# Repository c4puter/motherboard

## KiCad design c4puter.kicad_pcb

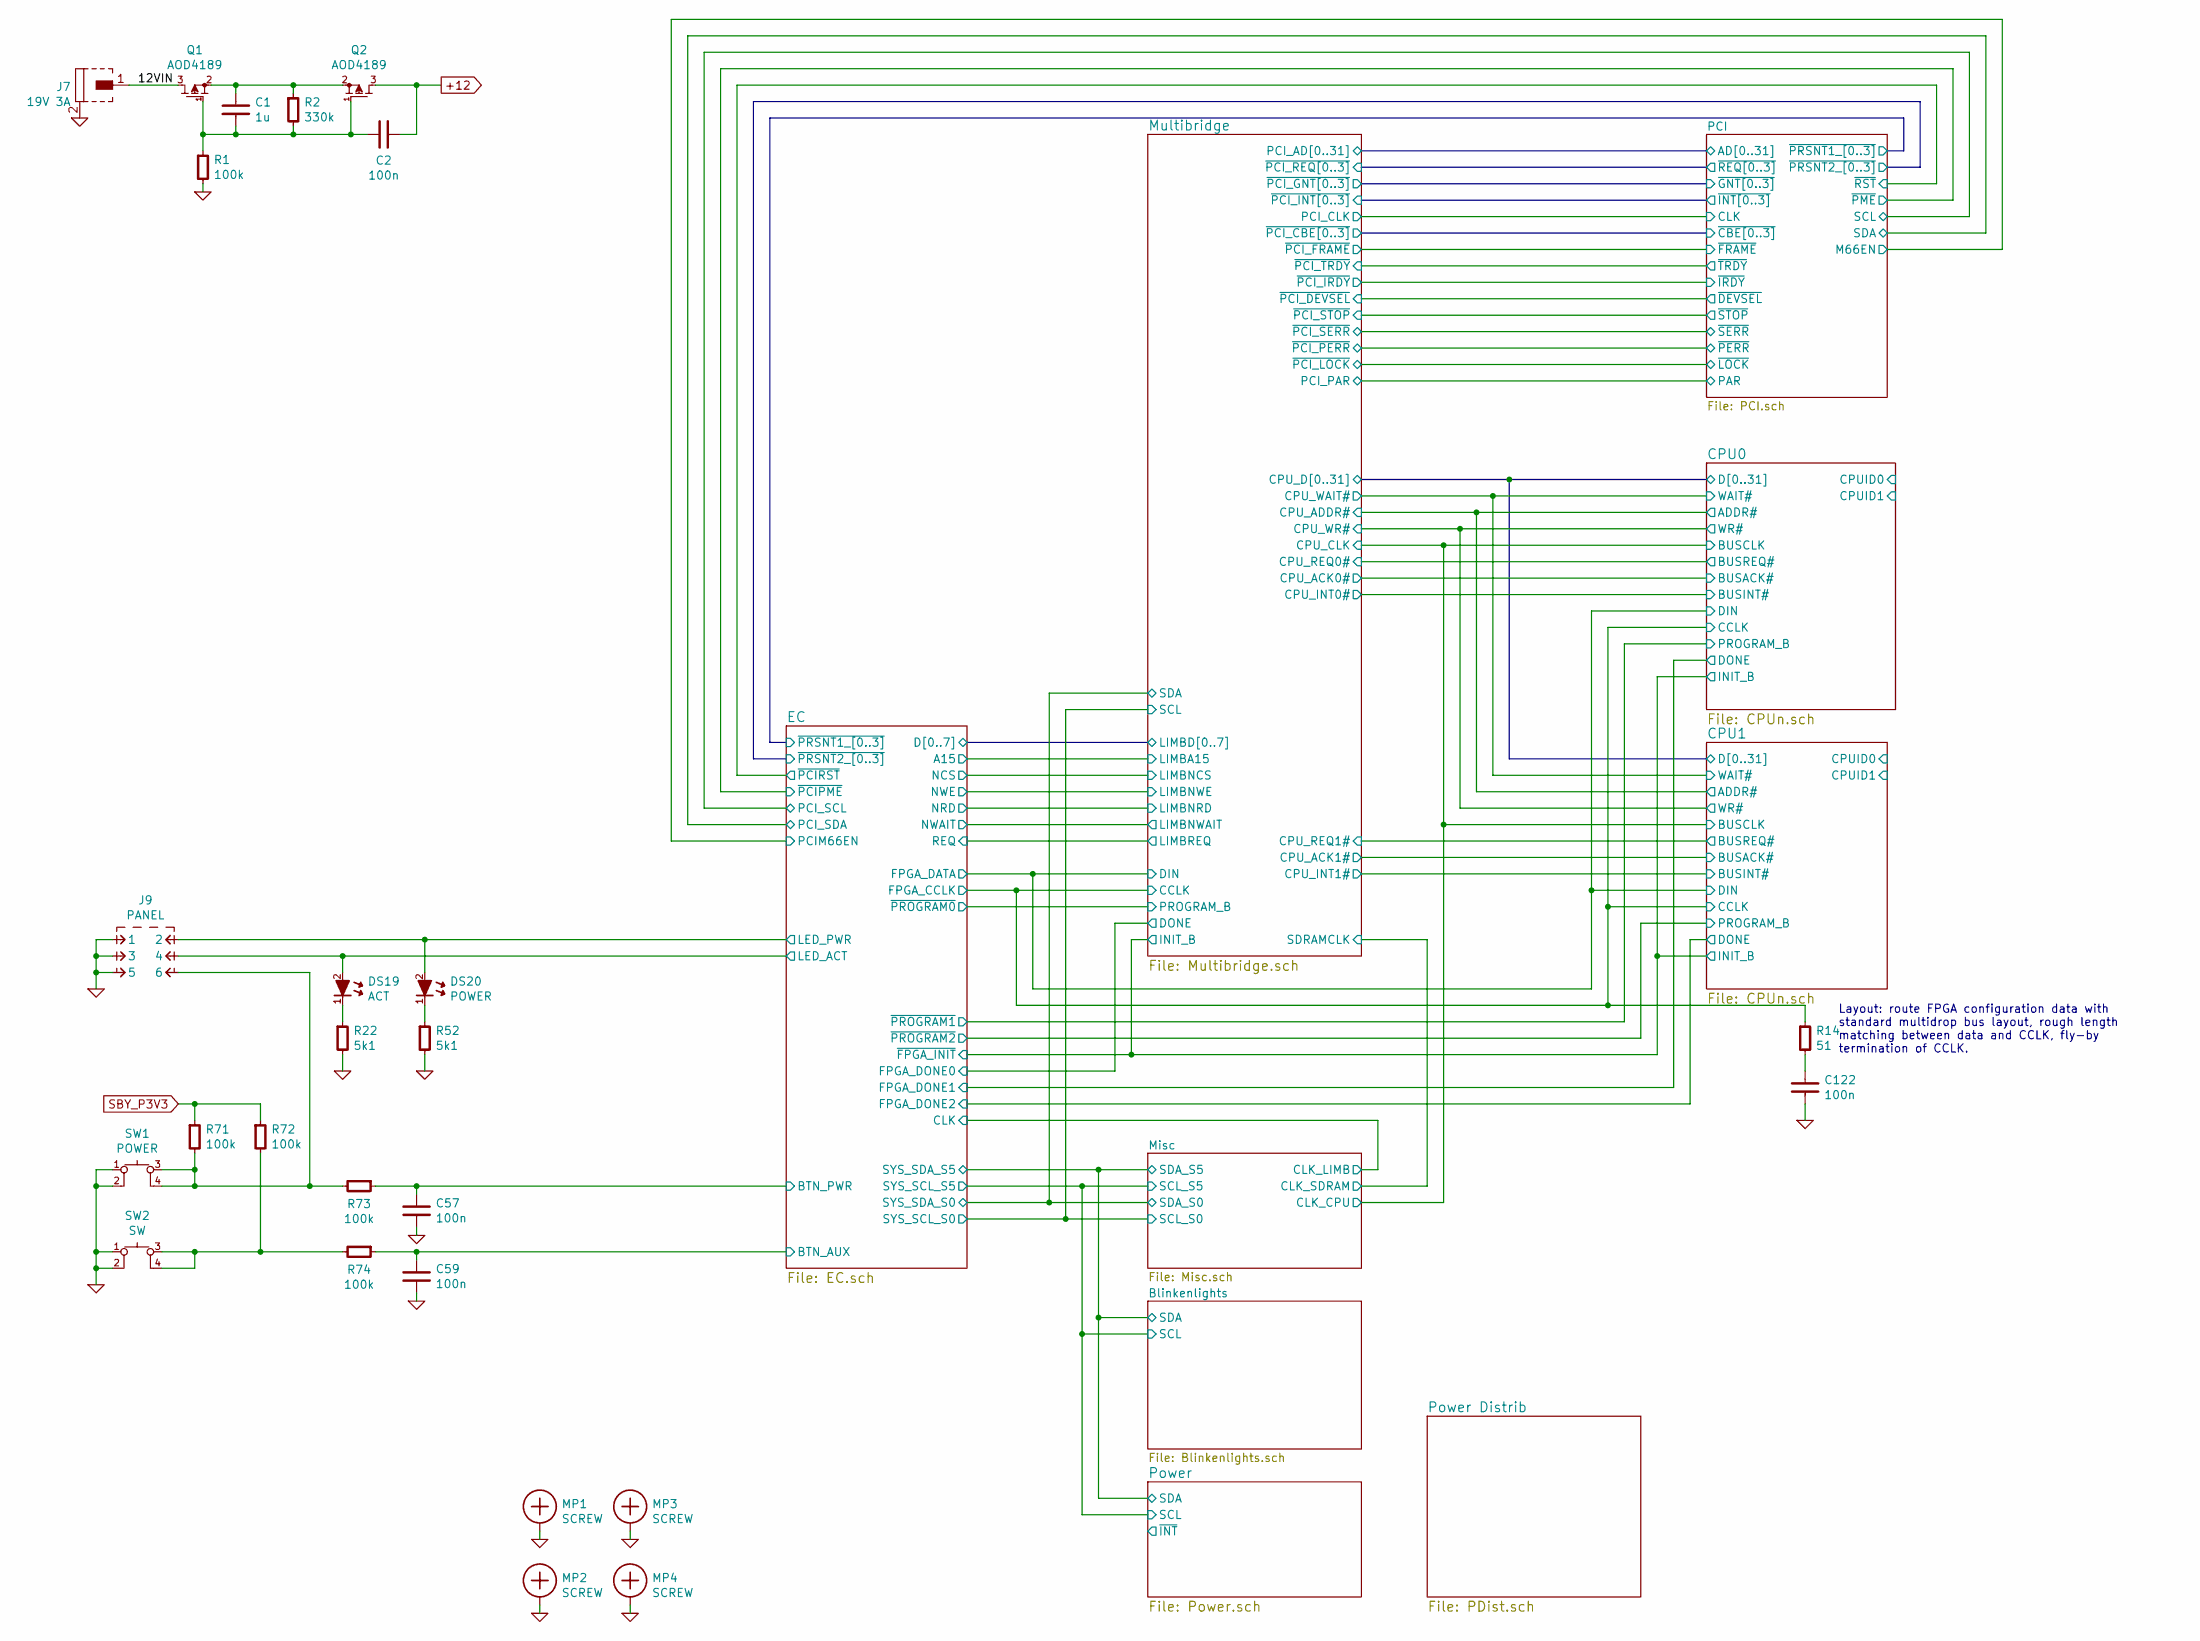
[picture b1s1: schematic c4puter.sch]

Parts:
C1: 1u; CAPC2012X70
C2, C57, C59, C122: 100n; CAPC1005X55
DS19: ACT; LED-0603
DS20: POWER; LED-0603
J7: 19V 3A; CONN-PJ-037A
J9: PANEL; CONN-100MIL-M-2x3
MP1, MP2, MP3, MP4: SCREW; SCREW-4-SUPPORTED
Q1, Q2: AOD4189; TO-252
R1, R71, R72, R73, R74: 100k; RESC1608X50
R2: 330k; RESC1608X50
R14: 51; RESC1005X40
R22, R52: 5k1; RESC1005X40
SW1: POWER; CK-PTS645-SMD
SW2: SW; CK-PTS645-SMD

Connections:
+12: C2.1, Q2.3 (D); also elsewhere on the board
/12VIN: J7.1, Q1.3 (D)
/CPU0/CCLK: R14.1; also elsewhere on the board
/EC/BTN_AUX: C59.1, R74.1
/EC/BTN_PWR: C57.1, R73.1
/EC/LED_ACT: DS19.2 (A), J9.4
/EC/LED_PWR: DS20.2 (A), J9.2
GND: C57.2, C59.2, C122.2, J7.2, J9.1, J9.3, J9.5, MP1.1, MP2.1, MP3.1, MP4.1, R1.2, R22.2, R52.2, SW1.1, SW1.2, SW2.1, SW2.2; also elsewhere on the board
unnamed: C1.1, Q1.2 (S), Q2.2 (S), R2.1
unnamed: C1.2, C2.2, Q1.1 (G), Q2.1 (G), R1.1, R2.2
unnamed: C122.1, R14.2
unnamed: DS19.1 (K), R22.1
unnamed: DS20.1 (K), R52.1
unnamed: J9.6, R71.2, R73.2, SW1.3, SW1.4
unnamed: R72.2, R74.2, SW2.3, SW2.4
SBY_P3V3: R71.1, R72.1

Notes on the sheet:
Layout: route FPGA configuration data with standard multidrop bus layout, rough length matching between data and CCLK, fly-by termination of CCLK.

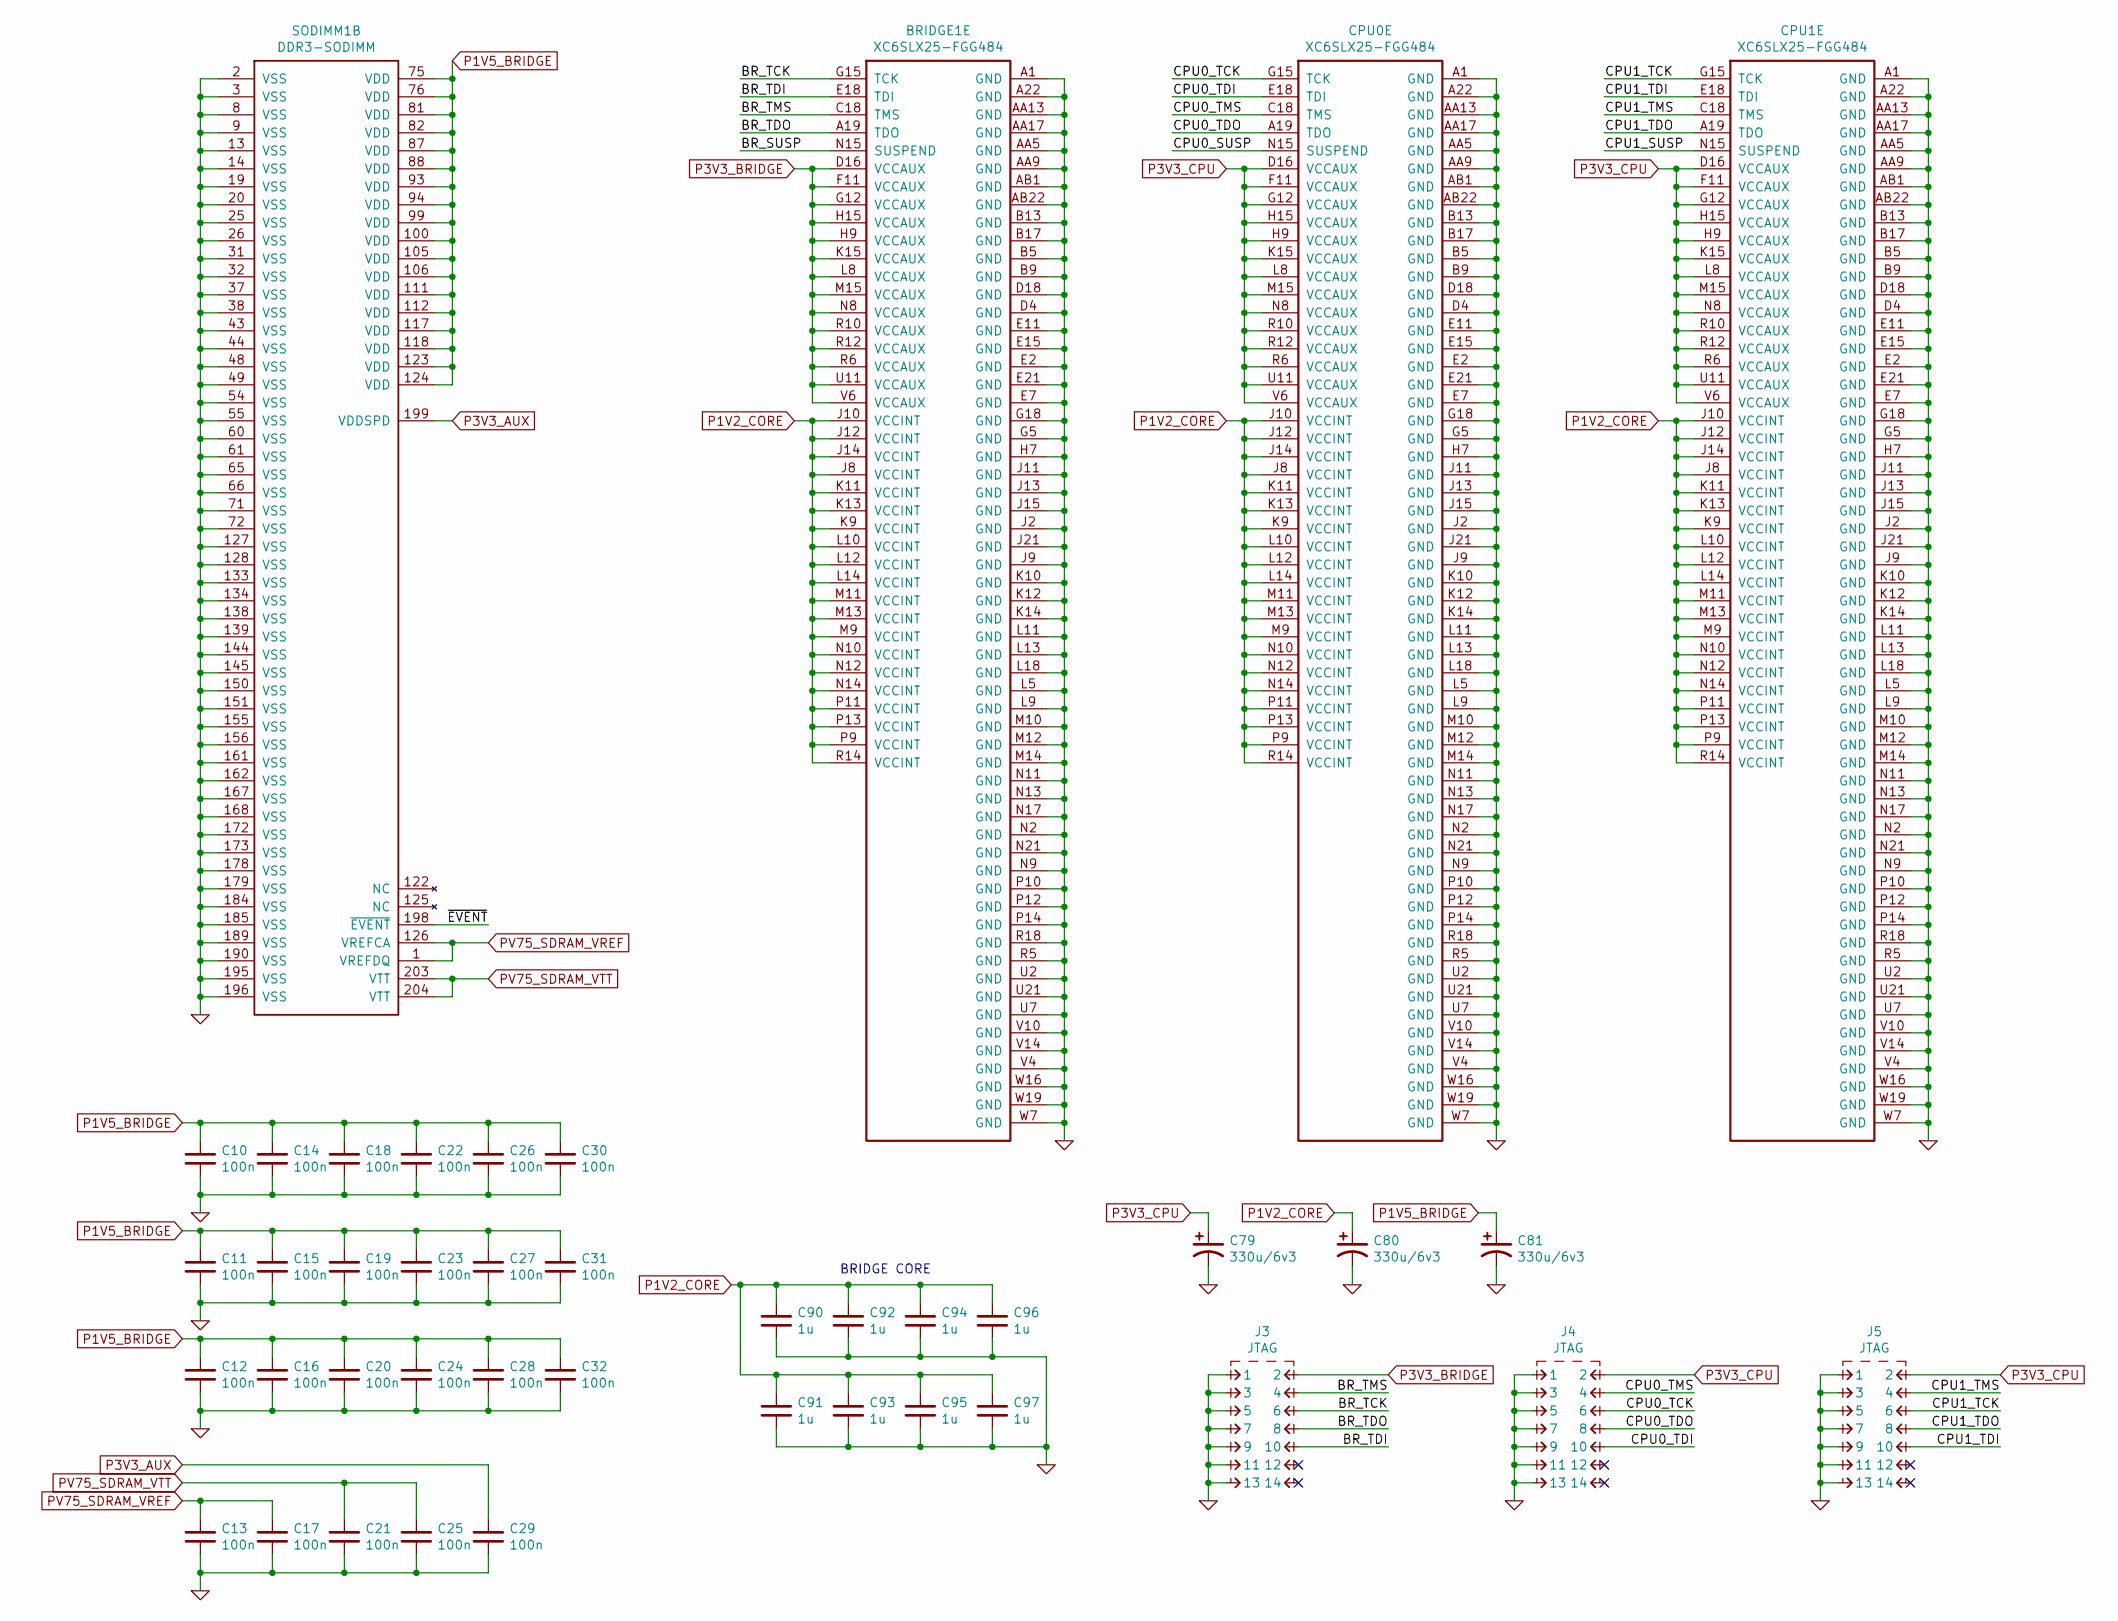
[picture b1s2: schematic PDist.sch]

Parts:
BRIDGE1: XC6SLX25-FGG484; XILINX-FGG484
C10, C11, C12, C13, C14, C15, C16, C17, C18, C19, C20, C21, C22, C23, C24, C25, C26, C27, C28, C29, C30, C31, C32: 100n; CAPC1005X55
C79, C80, C81: 330u/6v3; CAPMP6032X280
C90, C91, C92, C93, C94, C95, C96, C97: 1u; CAPC1005X55
CPU0, CPU1: XC6SLX25-FGG484; XILINX-FGG484
J3, J4, J5: JTAG; 98424-G52-14ALF
SODIMM1: DDR3-SODIMM

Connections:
/Power Distrib/BR_SUSP: BRIDGE1.N15 (SUSPEND)
/Power Distrib/BR_TCK: BRIDGE1.G15 (TCK), J3.6
/Power Distrib/BR_TDI: BRIDGE1.E18 (TDI), J3.10
/Power Distrib/BR_TDO: BRIDGE1.A19 (TDO), J3.8
/Power Distrib/BR_TMS: BRIDGE1.C18 (TMS), J3.4
/Power Distrib/CPU0_SUSP: CPU0.N15 (SUSPEND)
/Power Distrib/CPU0_TCK: CPU0.G15 (TCK), J4.6
/Power Distrib/CPU0_TDI: CPU0.E18 (TDI), J4.10
/Power Distrib/CPU0_TDO: CPU0.A19 (TDO), J4.8
/Power Distrib/CPU0_TMS: CPU0.C18 (TMS), J4.4
/Power Distrib/CPU1_SUSP: CPU1.N15 (SUSPEND)
/Power Distrib/CPU1_TCK: CPU1.G15 (TCK), J5.6
/Power Distrib/CPU1_TDI: CPU1.E18 (TDI), J5.10
/Power Distrib/CPU1_TDO: CPU1.A19 (TDO), J5.8
/Power Distrib/CPU1_TMS: CPU1.C18 (TMS), J5.4
/Power Distrib/~EVENT: SODIMM1.198 (~EVENT)
GND: BRIDGE1.A1 (GND), BRIDGE1.A22 (GND), BRIDGE1.AA5 (GND), BRIDGE1.AA9 (GND), BRIDGE1.AA13 (GND), BRIDGE1.AA17 (GND), BRIDGE1.AB1 (GND), BRIDGE1.AB22 (GND), BRIDGE1.B5 (GND), BRIDGE1.B9 (GND), BRIDGE1.B13 (GND), BRIDGE1.B17 (GND), BRIDGE1.D4 (GND), BRIDGE1.D18 (GND), BRIDGE1.E2 (GND), BRIDGE1.E7 (GND), BRIDGE1.E11 (GND), BRIDGE1.E15 (GND), BRIDGE1.E21 (GND), BRIDGE1.G5 (GND), BRIDGE1.G18 (GND), BRIDGE1.H7 (GND), BRIDGE1.J2 (GND), BRIDGE1.J9 (GND), BRIDGE1.J11 (GND), BRIDGE1.J13 (GND), BRIDGE1.J15 (GND), BRIDGE1.J21 (GND), BRIDGE1.K10 (GND), BRIDGE1.K12 (GND), BRIDGE1.K14 (GND), BRIDGE1.L5 (GND), BRIDGE1.L9 (GND), BRIDGE1.L11 (GND), BRIDGE1.L13 (GND), BRIDGE1.L18 (GND), BRIDGE1.M10 (GND), BRIDGE1.M12 (GND), BRIDGE1.M14 (GND), BRIDGE1.N2 (GND), BRIDGE1.N9 (GND), BRIDGE1.N11 (GND), BRIDGE1.N13 (GND), BRIDGE1.N17 (GND), BRIDGE1.N21 (GND), BRIDGE1.P10 (GND), BRIDGE1.P12 (GND), BRIDGE1.P14 (GND), BRIDGE1.R5 (GND), BRIDGE1.R18 (GND), BRIDGE1.U2 (GND), BRIDGE1.U7 (GND), BRIDGE1.U21 (GND), BRIDGE1.V4 (GND), BRIDGE1.V10 (GND), BRIDGE1.V14 (GND), BRIDGE1.W7 (GND), BRIDGE1.W16 (GND), BRIDGE1.W19 (GND), C10.2, C11.2, C12.2, C13.2, C14.2, C15.2, C16.2, C17.2, C18.2, C19.2, C20.2, C21.2, C22.2, C23.2, C24.2, C25.2, C26.2, C27.2, C28.2, C29.2, C30.2, C31.2, C32.2, C79.2, C80.2, C81.2, C90.2, C91.2, C92.2, C93.2, C94.2, C95.2, C96.2, C97.2, CPU0.A1 (GND), CPU0.A22 (GND), CPU0.AA5 (GND), CPU0.AA9 (GND), CPU0.AA13 (GND), CPU0.AA17 (GND), CPU0.AB1 (GND), CPU0.AB22 (GND), CPU0.B5 (GND), CPU0.B9 (GND), CPU0.B13 (GND), CPU0.B17 (GND), CPU0.D4 (GND), CPU0.D18 (GND), CPU0.E2 (GND), CPU0.E7 (GND), CPU0.E11 (GND), CPU0.E15 (GND), CPU0.E21 (GND), CPU0.G5 (GND), CPU0.G18 (GND), CPU0.H7 (GND), CPU0.J2 (GND), CPU0.J9 (GND), CPU0.J11 (GND), CPU0.J13 (GND), CPU0.J15 (GND), CPU0.J21 (GND), CPU0.K10 (GND), CPU0.K12 (GND), CPU0.K14 (GND), CPU0.L5 (GND), CPU0.L9 (GND), CPU0.L11 (GND), CPU0.L13 (GND), CPU0.L18 (GND), CPU0.M10 (GND), CPU0.M12 (GND), CPU0.M14 (GND), CPU0.N2 (GND), CPU0.N9 (GND), CPU0.N11 (GND), CPU0.N13 (GND), CPU0.N17 (GND), CPU0.N21 (GND), CPU0.P10 (GND), CPU0.P12 (GND), CPU0.P14 (GND), CPU0.R5 (GND), CPU0.R18 (GND), CPU0.U2 (GND), CPU0.U7 (GND), CPU0.U21 (GND), CPU0.V4 (GND), CPU0.V10 (GND), CPU0.V14 (GND), CPU0.W7 (GND), CPU0.W16 (GND), CPU0.W19 (GND), CPU1.A1 (GND), CPU1.A22 (GND), CPU1.AA5 (GND), CPU1.AA9 (GND), CPU1.AA13 (GND), CPU1.AA17 (GND), CPU1.AB1 (GND), CPU1.AB22 (GND), CPU1.B5 (GND), CPU1.B9 (GND), CPU1.B13 (GND), CPU1.B17 (GND), CPU1.D4 (GND), CPU1.D18 (GND), CPU1.E2 (GND), CPU1.E7 (GND), CPU1.E11 (GND), CPU1.E15 (GND), CPU1.E21 (GND), CPU1.G5 (GND), CPU1.G18 (GND), CPU1.H7 (GND), CPU1.J2 (GND), CPU1.J9 (GND), CPU1.J11 (GND), CPU1.J13 (GND), CPU1.J15 (GND), CPU1.J21 (GND), CPU1.K10 (GND), CPU1.K12 (GND), CPU1.K14 (GND), CPU1.L5 (GND), CPU1.L9 (GND), CPU1.L11 (GND), CPU1.L13 (GND), CPU1.L18 (GND), CPU1.M10 (GND), CPU1.M12 (GND), CPU1.M14 (GND), CPU1.N2 (GND), CPU1.N9 (GND), CPU1.N11 (GND), CPU1.N13 (GND), CPU1.N17 (GND), CPU1.N21 (GND), CPU1.P10 (GND), CPU1.P12 (GND), CPU1.P14 (GND), CPU1.R5 (GND), CPU1.R18 (GND), CPU1.U2 (GND), CPU1.U7 (GND), CPU1.U21 (GND), CPU1.V4 (GND), CPU1.V10 (GND), CPU1.V14 (GND), CPU1.W7 (GND), CPU1.W16 (GND), CPU1.W19 (GND), J3.1, J3.3, J3.5, J3.7, J3.9, J3.11, J3.13, J4.1, J4.3, J4.5, J4.7, J4.9, J4.11, J4.13, J5.1, J5.3, J5.5, J5.7, J5.9, J5.11, J5.13, SODIMM1.2 (VSS), SODIMM1.3 (VSS), SODIMM1.8 (VSS), SODIMM1.9 (VSS), SODIMM1.13 (VSS), SODIMM1.14 (VSS), SODIMM1.19 (VSS), SODIMM1.20 (VSS), SODIMM1.25 (VSS), SODIMM1.26 (VSS), SODIMM1.31 (VSS), SODIMM1.32 (VSS), SODIMM1.37 (VSS), SODIMM1.38 (VSS), SODIMM1.43 (VSS), SODIMM1.44 (VSS), SODIMM1.48 (VSS), SODIMM1.49 (VSS), SODIMM1.54 (VSS), SODIMM1.55 (VSS), SODIMM1.60 (VSS), SODIMM1.61 (VSS), SODIMM1.65 (VSS), SODIMM1.66 (VSS), SODIMM1.71 (VSS), SODIMM1.72 (VSS), SODIMM1.127 (VSS), SODIMM1.128 (VSS), SODIMM1.133 (VSS), SODIMM1.134 (VSS), SODIMM1.138 (VSS), SODIMM1.139 (VSS), SODIMM1.144 (VSS), SODIMM1.145 (VSS), SODIMM1.150 (VSS), SODIMM1.151 (VSS), SODIMM1.155 (VSS), SODIMM1.156 (VSS), SODIMM1.161 (VSS), SODIMM1.162 (VSS), SODIMM1.167 (VSS), SODIMM1.168 (VSS), SODIMM1.172 (VSS), SODIMM1.173 (VSS), SODIMM1.178 (VSS), SODIMM1.179 (VSS), SODIMM1.184 (VSS), SODIMM1.185 (VSS), SODIMM1.189 (VSS), SODIMM1.190 (VSS), SODIMM1.195 (VSS), SODIMM1.196 (VSS); also elsewhere on the board
P1V2_CORE: BRIDGE1.J8 (VCCINT), BRIDGE1.J10 (VCCINT), BRIDGE1.J12 (VCCINT), BRIDGE1.J14 (VCCINT), BRIDGE1.K9 (VCCINT), BRIDGE1.K11 (VCCINT), BRIDGE1.K13 (VCCINT), BRIDGE1.L10 (VCCINT), BRIDGE1.L12 (VCCINT), BRIDGE1.L14 (VCCINT), BRIDGE1.M9 (VCCINT), BRIDGE1.M11 (VCCINT), BRIDGE1.M13 (VCCINT), BRIDGE1.N10 (VCCINT), BRIDGE1.N12 (VCCINT), BRIDGE1.N14 (VCCINT), BRIDGE1.P9 (VCCINT), BRIDGE1.P11 (VCCINT), BRIDGE1.P13 (VCCINT), BRIDGE1.R14 (VCCINT), C80.1, C90.1, C91.1, C92.1, C93.1, C94.1, C95.1, C96.1, C97.1, CPU0.J8 (VCCINT), CPU0.J10 (VCCINT), CPU0.J12 (VCCINT), CPU0.J14 (VCCINT), CPU0.K9 (VCCINT), CPU0.K11 (VCCINT), CPU0.K13 (VCCINT), CPU0.L10 (VCCINT), CPU0.L12 (VCCINT), CPU0.L14 (VCCINT), CPU0.M9 (VCCINT), CPU0.M11 (VCCINT), CPU0.M13 (VCCINT), CPU0.N10 (VCCINT), CPU0.N12 (VCCINT), CPU0.N14 (VCCINT), CPU0.P9 (VCCINT), CPU0.P11 (VCCINT), CPU0.P13 (VCCINT), CPU0.R14 (VCCINT), CPU1.J8 (VCCINT), CPU1.J10 (VCCINT), CPU1.J12 (VCCINT), CPU1.J14 (VCCINT), CPU1.K9 (VCCINT), CPU1.K11 (VCCINT), CPU1.K13 (VCCINT), CPU1.L10 (VCCINT), CPU1.L12 (VCCINT), CPU1.L14 (VCCINT), CPU1.M9 (VCCINT), CPU1.M11 (VCCINT), CPU1.M13 (VCCINT), CPU1.N10 (VCCINT), CPU1.N12 (VCCINT), CPU1.N14 (VCCINT), CPU1.P9 (VCCINT), CPU1.P11 (VCCINT), CPU1.P13 (VCCINT), CPU1.R14 (VCCINT); also elsewhere on the board
P1V5_BRIDGE: C10.1, C11.1, C12.1, C14.1, C15.1, C16.1, C18.1, C19.1, C20.1, C22.1, C23.1, C24.1, C26.1, C27.1, C28.1, C30.1, C31.1, C32.1, C81.1, SODIMM1.75 (VDD), SODIMM1.76 (VDD), SODIMM1.81 (VDD), SODIMM1.82 (VDD), SODIMM1.87 (VDD), SODIMM1.88 (VDD), SODIMM1.93 (VDD), SODIMM1.94 (VDD), SODIMM1.99 (VDD), SODIMM1.100 (VDD), SODIMM1.105 (VDD), SODIMM1.106 (VDD), SODIMM1.111 (VDD), SODIMM1.112 (VDD), SODIMM1.117 (VDD), SODIMM1.118 (VDD), SODIMM1.123 (VDD), SODIMM1.124 (VDD); also elsewhere on the board
P3V3_AUX: C29.1, SODIMM1.199 (VDDSPD); also elsewhere on the board
P3V3_BRIDGE: BRIDGE1.D16 (VCCAUX), BRIDGE1.F11 (VCCAUX), BRIDGE1.G12 (VCCAUX), BRIDGE1.H9 (VCCAUX), BRIDGE1.H15 (VCCAUX), BRIDGE1.K15 (VCCAUX), BRIDGE1.L8 (VCCAUX), BRIDGE1.M15 (VCCAUX), BRIDGE1.N8 (VCCAUX), BRIDGE1.R6 (VCCAUX), BRIDGE1.R10 (VCCAUX), BRIDGE1.R12 (VCCAUX), BRIDGE1.U11 (VCCAUX), BRIDGE1.V6 (VCCAUX), J3.2; also elsewhere on the board
P3V3_CPU: C79.1, CPU0.D16 (VCCAUX), CPU0.F11 (VCCAUX), CPU0.G12 (VCCAUX), CPU0.H9 (VCCAUX), CPU0.H15 (VCCAUX), CPU0.K15 (VCCAUX), CPU0.L8 (VCCAUX), CPU0.M15 (VCCAUX), CPU0.N8 (VCCAUX), CPU0.R6 (VCCAUX), CPU0.R10 (VCCAUX), CPU0.R12 (VCCAUX), CPU0.U11 (VCCAUX), CPU0.V6 (VCCAUX), CPU1.D16 (VCCAUX), CPU1.F11 (VCCAUX), CPU1.G12 (VCCAUX), CPU1.H9 (VCCAUX), CPU1.H15 (VCCAUX), CPU1.K15 (VCCAUX), CPU1.L8 (VCCAUX), CPU1.M15 (VCCAUX), CPU1.N8 (VCCAUX), CPU1.R6 (VCCAUX), CPU1.R10 (VCCAUX), CPU1.R12 (VCCAUX), CPU1.U11 (VCCAUX), CPU1.V6 (VCCAUX), J4.2, J5.2; also elsewhere on the board
PV75_SDRAM_VREF: C13.1, C17.1, SODIMM1.1 (VREFDQ), SODIMM1.126 (VREFCA); also elsewhere on the board
PV75_SDRAM_VTT: C21.1, C25.1, SODIMM1.203 (VTT), SODIMM1.204 (VTT); also elsewhere on the board

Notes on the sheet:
BRIDGE CORE

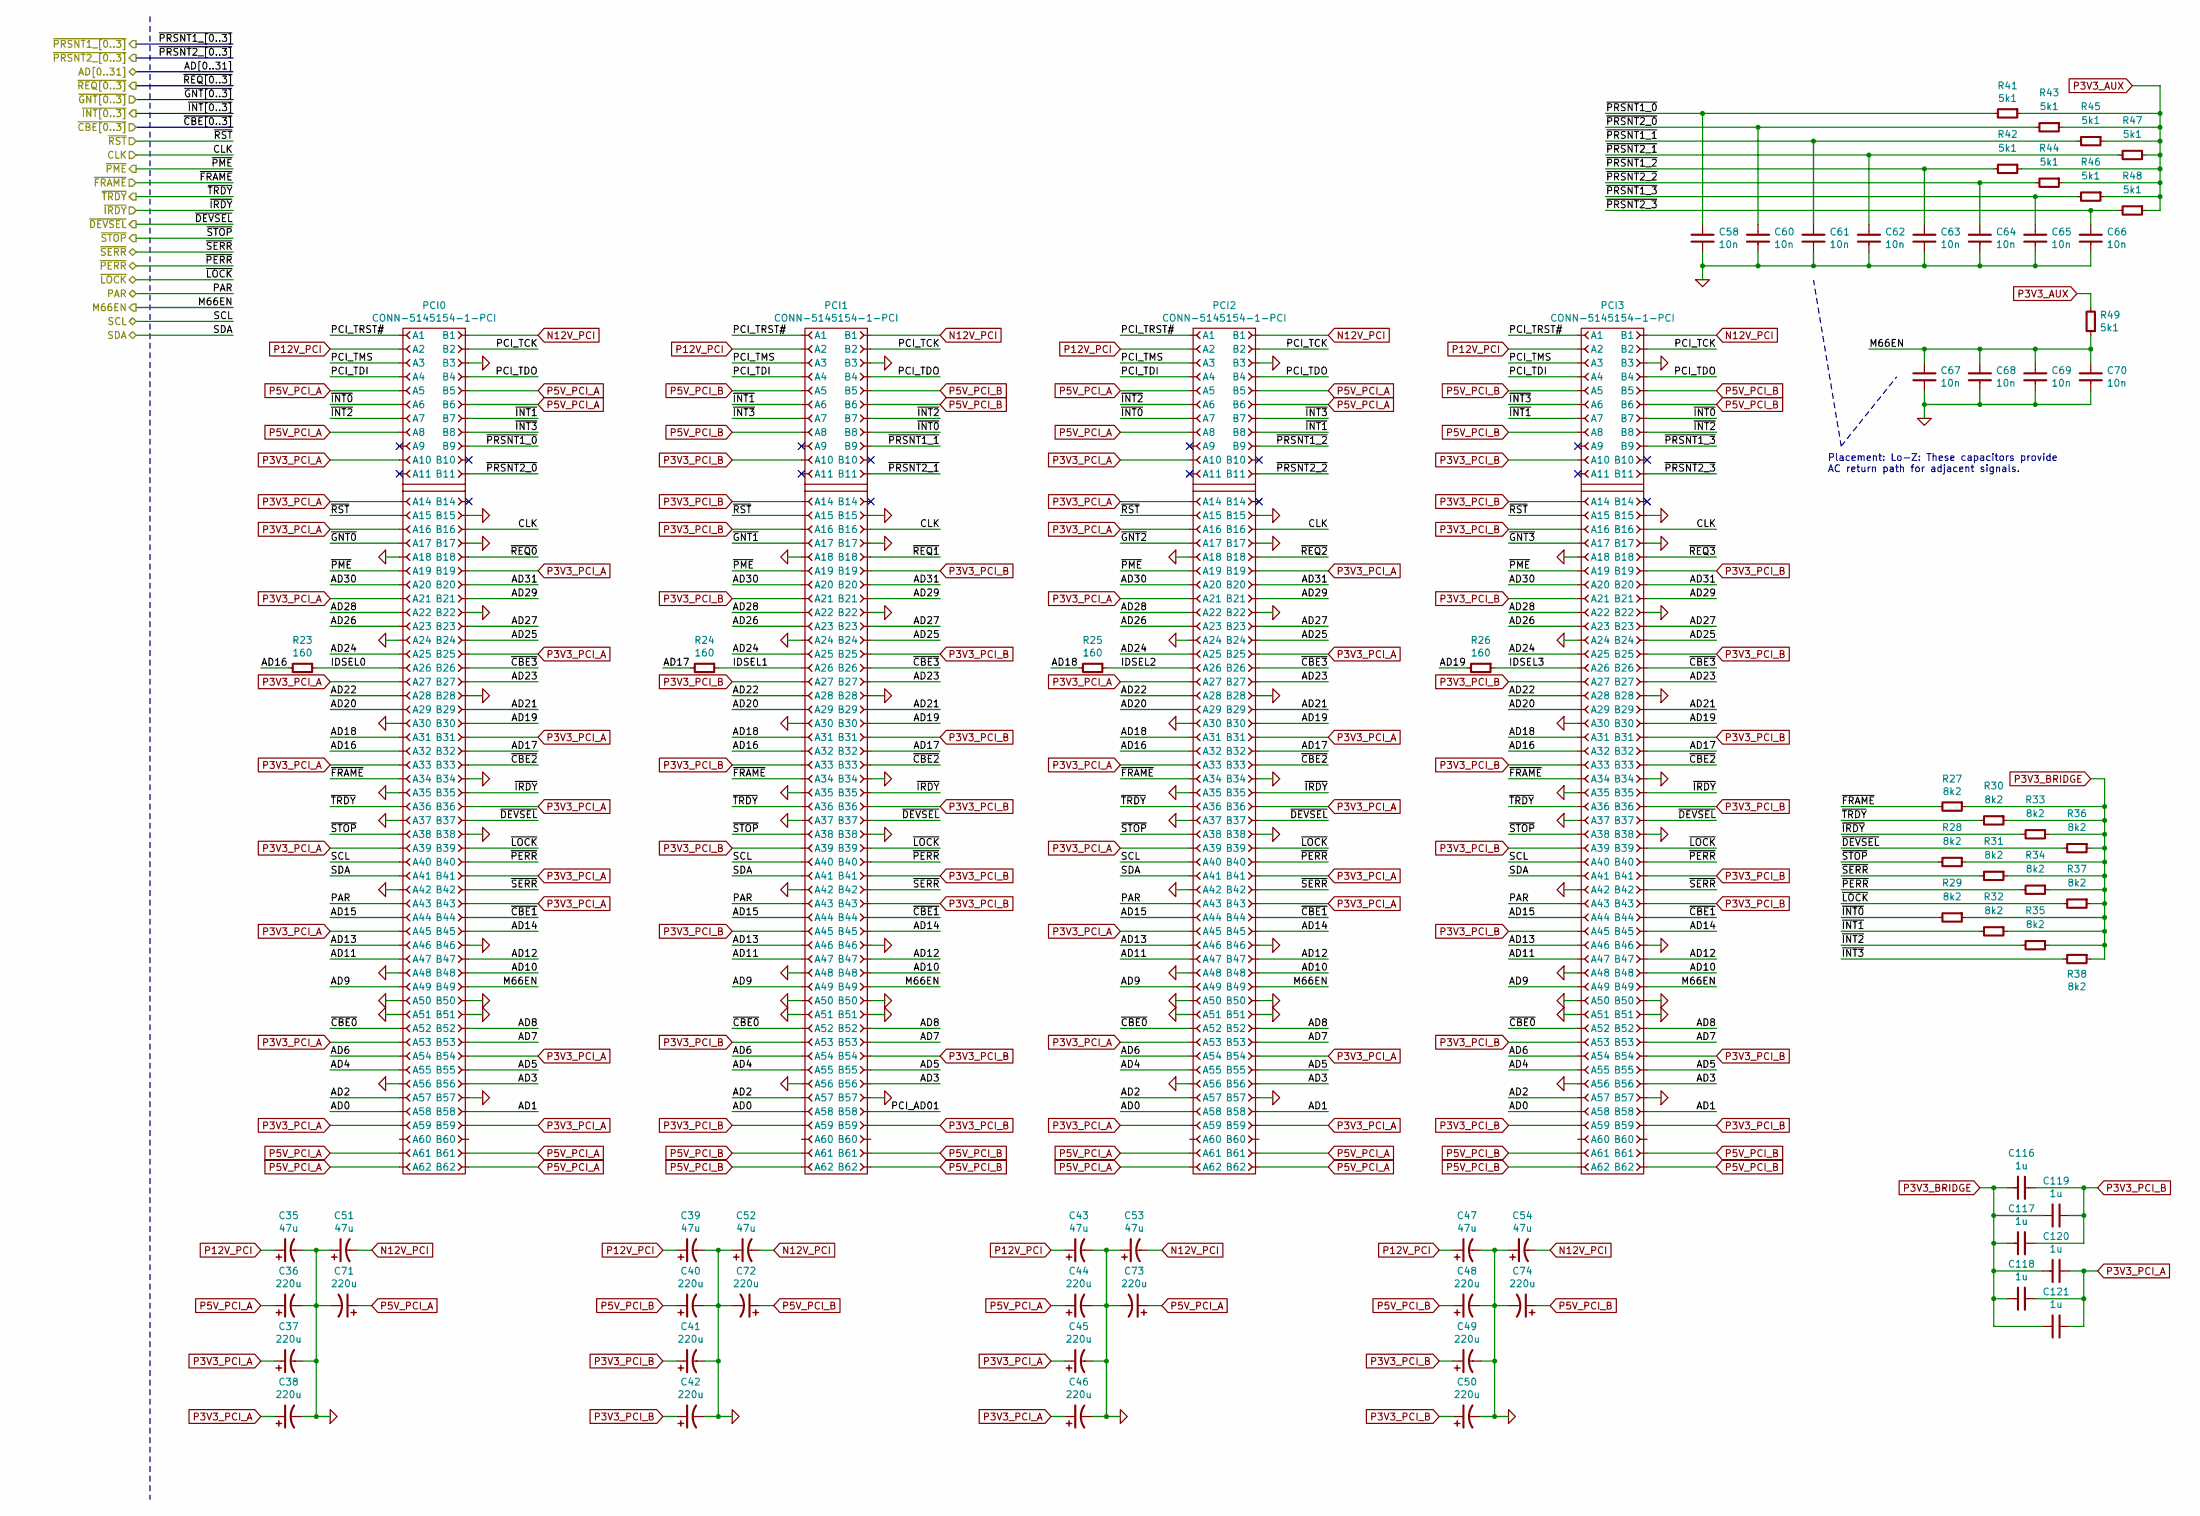
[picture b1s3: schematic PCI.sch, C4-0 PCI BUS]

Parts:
C35, C39, C43, C47, C51, C52, C53, C54: 47u; C-ALUM-6.3mm
C36, C37, C38, C40, C41, C42, C44, C45, C46, C48, C49, C50, C71, C72, C73, C74: 220u; C-ALUM-6.3mm
C58, C60, C61, C62, C63, C64, C65, C66, C67, C68, C69, C70: 10n; CAPC1005X55
C116, C117, C118, C119, C120, C121: 1u; CAPC1005X55
PCI0, PCI1, PCI2, PCI3: CONN-5145154-1-PCI; 5145154-1
R23, R24, R25, R26: 160; RESC1608X50
R27, R28, R29, R30, R31, R32, R33, R34, R35, R36, R37, R38: 8k2; RESC1608X50
R41, R42, R43, R44, R45, R46, R47, R48, R49: 5k1; RESC1608X50

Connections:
/EC/PCI_SCL: PCI0.A40, PCI1.A40, PCI2.A40, PCI3.A40; also elsewhere on the board
/EC/PCI_SDA: PCI0.A41, PCI1.A41, PCI2.A41, PCI3.A41; also elsewhere on the board
/EC/~PCIPME: PCI0.A19, PCI1.A19, PCI2.A19, PCI3.A19; also elsewhere on the board
/EC/~PCIRST: PCI0.A15, PCI1.A15, PCI2.A15, PCI3.A15; also elsewhere on the board
/EC/~PRSNT1_0: C58.1, PCI0.B9, R41.2; also elsewhere on the board
/EC/~PRSNT1_1: C61.1, PCI1.B9, R45.2; also elsewhere on the board
/EC/~PRSNT1_2: C63.1, PCI2.B9, R42.2; also elsewhere on the board
/EC/~PRSNT1_3: C65.1, PCI3.B9, R46.2; also elsewhere on the board
/EC/~PRSNT2_0: C60.1, PCI0.B11, R43.2; also elsewhere on the board
/EC/~PRSNT2_1: C62.1, PCI1.B11, R47.2; also elsewhere on the board
/EC/~PRSNT2_2: C64.1, PCI2.B11, R44.2; also elsewhere on the board
/EC/~PRSNT2_3: C66.1, PCI3.B11, R48.2; also elsewhere on the board
/Multibridge/~PCI_PERR: PCI0.B40, PCI1.B40, PCI2.B40, PCI3.B40, R34.2; also elsewhere on the board
/Multibridge/~PCI_REQ0: PCI0.B18; also elsewhere on the board
/Multibridge/~PCI_REQ1: PCI1.B18; also elsewhere on the board
/Multibridge/~PCI_REQ2: PCI2.B18; also elsewhere on the board
/Multibridge/~PCI_REQ3: PCI3.B18; also elsewhere on the board
/Multibridge/~PCI_SERR: PCI0.B42, PCI1.B42, PCI2.B42, PCI3.B42, R31.2; also elsewhere on the board
/Multibridge/~PCI_STOP: PCI0.A38, PCI1.A38, PCI2.A38, PCI3.A38, R28.2; also elsewhere on the board
/Multibridge/~PCI_TRDY: PCI0.A36, PCI1.A36, PCI2.A36, PCI3.A36, R30.2; also elsewhere on the board
/PCI/AD0: PCI0.A58, PCI1.A58, PCI2.A58, PCI3.A58; also elsewhere on the board
/PCI/AD1: PCI0.B58, PCI2.B58, PCI3.B58; also elsewhere on the board
/PCI/AD2: PCI0.A57, PCI1.A57, PCI2.A57, PCI3.A57; also elsewhere on the board
/PCI/AD3: PCI0.B56, PCI1.B56, PCI2.B56, PCI3.B56; also elsewhere on the board
/PCI/AD4: PCI0.A55, PCI1.A55, PCI2.A55, PCI3.A55; also elsewhere on the board
/PCI/AD5: PCI0.B55, PCI1.B55, PCI2.B55, PCI3.B55; also elsewhere on the board
/PCI/AD6: PCI0.A54, PCI1.A54, PCI2.A54, PCI3.A54; also elsewhere on the board
/PCI/AD7: PCI0.B53, PCI1.B53, PCI2.B53, PCI3.B53; also elsewhere on the board
/PCI/AD8: PCI0.B52, PCI1.B52, PCI2.B52, PCI3.B52; also elsewhere on the board
/PCI/AD9: PCI0.A49, PCI1.A49, PCI2.A49, PCI3.A49; also elsewhere on the board
/PCI/AD10: PCI0.B48, PCI1.B48, PCI2.B48, PCI3.B48; also elsewhere on the board
/PCI/AD11: PCI0.A47, PCI1.A47, PCI2.A47, PCI3.A47; also elsewhere on the board
/PCI/AD12: PCI0.B47, PCI1.B47, PCI2.B47, PCI3.B47; also elsewhere on the board
/PCI/AD13: PCI0.A46, PCI1.A46, PCI2.A46, PCI3.A46; also elsewhere on the board
/PCI/AD14: PCI0.B45, PCI1.B45, PCI2.B45, PCI3.B45; also elsewhere on the board
/PCI/AD15: PCI0.A44, PCI1.A44, PCI2.A44, PCI3.A44; also elsewhere on the board
/PCI/AD16: PCI0.A32, PCI1.A32, PCI2.A32, PCI3.A32, R23.2; also elsewhere on the board
/PCI/AD17: PCI0.B32, PCI1.B32, PCI2.B32, PCI3.B32, R24.2; also elsewhere on the board
/PCI/AD18: PCI0.A31, PCI1.A31, PCI2.A31, PCI3.A31, R25.2; also elsewhere on the board
/PCI/AD19: PCI0.B30, PCI1.B30, PCI2.B30, PCI3.B30, R26.2; also elsewhere on the board
/PCI/AD20: PCI0.A29, PCI1.A29, PCI2.A29, PCI3.A29; also elsewhere on the board
/PCI/AD21: PCI0.B29, PCI1.B29, PCI2.B29, PCI3.B29; also elsewhere on the board
/PCI/AD22: PCI0.A28, PCI1.A28, PCI2.A28, PCI3.A28; also elsewhere on the board
/PCI/AD23: PCI0.B27, PCI1.B27, PCI2.B27, PCI3.B27; also elsewhere on the board
/PCI/AD24: PCI0.A25, PCI1.A25, PCI2.A25, PCI3.A25; also elsewhere on the board
/PCI/AD25: PCI0.B24, PCI1.B24, PCI2.B24, PCI3.B24; also elsewhere on the board
/PCI/AD26: PCI0.A23, PCI1.A23, PCI2.A23, PCI3.A23; also elsewhere on the board
/PCI/AD27: PCI0.B23, PCI1.B23, PCI2.B23, PCI3.B23; also elsewhere on the board
/PCI/AD28: PCI0.A22, PCI1.A22, PCI2.A22, PCI3.A22; also elsewhere on the board
/PCI/AD29: PCI0.B21, PCI1.B21, PCI2.B21, PCI3.B21; also elsewhere on the board
/PCI/AD30: PCI0.A20, PCI1.A20, PCI2.A20, PCI3.A20; also elsewhere on the board
/PCI/AD31: PCI0.B20, PCI1.B20, PCI2.B20, PCI3.B20; also elsewhere on the board
/PCI/CLK: PCI0.B16, PCI1.B16, PCI2.B16, PCI3.B16; also elsewhere on the board
/PCI/IDSEL0: PCI0.A26, R23.1
/PCI/IDSEL1: PCI1.A26, R24.1
/PCI/IDSEL2: PCI2.A26, R25.1
/PCI/IDSEL3: PCI3.A26, R26.1
/PCI/M66EN: C67.1, C68.1, C69.1, C70.1, PCI0.B49, PCI1.B49, PCI2.B49, PCI3.B49, R49.1; also elsewhere on the board
/PCI/PAR: PCI0.A43, PCI1.A43, PCI2.A43, PCI3.A43; also elsewhere on the board
/PCI/PCI_AD01: PCI1.B58
/PCI/PCI_TCK: PCI0.B2, PCI1.B2, PCI2.B2, PCI3.B2
/PCI/PCI_TDI: PCI0.A4, PCI1.A4, PCI2.A4, PCI3.A4
/PCI/PCI_TDO: PCI0.B4, PCI1.B4, PCI2.B4, PCI3.B4
/PCI/PCI_TMS: PCI0.A3, PCI1.A3, PCI2.A3, PCI3.A3
/PCI/PCI_TRST#: PCI0.A1, PCI1.A1, PCI2.A1, PCI3.A1
/PCI/~CBE0: PCI0.A52, PCI1.A52, PCI2.A52, PCI3.A52; also elsewhere on the board
/PCI/~CBE1: PCI0.B44, PCI1.B44, PCI2.B44, PCI3.B44; also elsewhere on the board
/PCI/~CBE2: PCI0.B33, PCI1.B33, PCI2.B33, PCI3.B33; also elsewhere on the board
/PCI/~CBE3: PCI0.B26, PCI1.B26, PCI2.B26, PCI3.B26; also elsewhere on the board
/PCI/~DEVSEL: PCI0.B37, PCI1.B37, PCI2.B37, PCI3.B37, R36.2; also elsewhere on the board
/PCI/~FRAME: PCI0.A34, PCI1.A34, PCI2.A34, PCI3.A34, R27.2; also elsewhere on the board
/PCI/~GNT0: PCI0.A17; also elsewhere on the board
/PCI/~GNT1: PCI1.A17; also elsewhere on the board
/PCI/~GNT2: PCI2.A17; also elsewhere on the board
/PCI/~GNT3: PCI3.A17; also elsewhere on the board
/PCI/~INT0: PCI0.A6, PCI1.B8, PCI2.A7, PCI3.B7, R29.2; also elsewhere on the board
/PCI/~INT1: PCI0.B7, PCI1.A6, PCI2.B8, PCI3.A7, R32.2; also elsewhere on the board
/PCI/~INT2: PCI0.A7, PCI1.B7, PCI2.A6, PCI3.B8, R35.2; also elsewhere on the board
/PCI/~INT3: PCI0.B8, PCI1.A7, PCI2.B7, PCI3.A6, R38.2; also elsewhere on the board
/PCI/~IRDY: PCI0.B35, PCI1.B35, PCI2.B35, PCI3.B35, R33.2; also elsewhere on the board
/PCI/~LOCK: PCI0.B39, PCI1.B39, PCI2.B39, PCI3.B39, R37.2; also elsewhere on the board
GND: C35.2, C36.2, C37.2, C38.2, C39.2, C40.2, C41.2, C42.2, C43.2, C44.2, C45.2, C46.2, C47.2, C48.2, C49.2, C50.2, C51.1, C52.1, C53.1, C54.1, C58.2, C60.2, C61.2, C62.2, C63.2, C64.2, C65.2, C66.2, C67.2, C68.2, C69.2, C70.2, C71.2, C72.2, C73.2, C74.2, PCI0.A18, PCI0.A24, PCI0.A30, PCI0.A35, PCI0.A37, PCI0.A42, PCI0.A48, PCI0.A50, PCI0.A51, PCI0.A56, PCI0.B3, PCI0.B15, PCI0.B17, PCI0.B22, PCI0.B28, PCI0.B34, PCI0.B38, PCI0.B46, PCI0.B50, PCI0.B51, PCI0.B57, PCI1.A18, PCI1.A24, PCI1.A30, PCI1.A35, PCI1.A37, PCI1.A42, PCI1.A48, PCI1.A50, PCI1.A51, PCI1.A56, PCI1.B3, PCI1.B15, PCI1.B17, PCI1.B22, PCI1.B28, PCI1.B34, PCI1.B38, PCI1.B46, PCI1.B50, PCI1.B51, PCI1.B57, PCI2.A18, PCI2.A24, PCI2.A30, PCI2.A35, PCI2.A37, PCI2.A42, PCI2.A48, PCI2.A50, PCI2.A51, PCI2.A56, PCI2.B3, PCI2.B15, PCI2.B17, PCI2.B22, PCI2.B28, PCI2.B34, PCI2.B38, PCI2.B46, PCI2.B50, PCI2.B51, PCI2.B57, PCI3.A18, PCI3.A24, PCI3.A30, PCI3.A35, PCI3.A37, PCI3.A42, PCI3.A48, PCI3.A50, PCI3.A51, PCI3.A56, PCI3.B3, PCI3.B15, PCI3.B17, PCI3.B22, PCI3.B28, PCI3.B34, PCI3.B38, PCI3.B46, PCI3.B50, PCI3.B51, PCI3.B57; also elsewhere on the board
N12V_PCI: C51.2, C52.2, C53.2, C54.2, PCI0.B1, PCI1.B1, PCI2.B1, PCI3.B1; also elsewhere on the board
P3V3_AUX: R41.1, R42.1, R43.1, R44.1, R45.1, R46.1, R47.1, R48.1, R49.2; also elsewhere on the board
P3V3_BRIDGE: C116.2, C117.2, C118.2, C119.2, C120.2, C121.2, R27.1, R28.1, R29.1, R30.1, R31.1, R32.1, R33.1, R34.1, R35.1, R36.1, R37.1, R38.1; also elsewhere on the board
P3V3_PCI_A: C37.1, C38.1, C45.1, C46.1, C118.1, C120.1, C121.1, PCI0.A10, PCI0.A14, PCI0.A16, PCI0.A21, PCI0.A27, PCI0.A33, PCI0.A39, PCI0.A45, PCI0.A53, PCI0.A59, PCI0.B19, PCI0.B25, PCI0.B31, PCI0.B36, PCI0.B41, PCI0.B43, PCI0.B54, PCI0.B59, PCI2.A10, PCI2.A14, PCI2.A16, PCI2.A21, PCI2.A27, PCI2.A33, PCI2.A39, PCI2.A45, PCI2.A53, PCI2.A59, PCI2.B19, PCI2.B25, PCI2.B31, PCI2.B36, PCI2.B41, PCI2.B43, PCI2.B54, PCI2.B59; also elsewhere on the board
P3V3_PCI_B: C41.1, C42.1, C49.1, C50.1, C116.1, C117.1, C119.1, PCI1.A10, PCI1.A14, PCI1.A16, PCI1.A21, PCI1.A27, PCI1.A33, PCI1.A39, PCI1.A45, PCI1.A53, PCI1.A59, PCI1.B19, PCI1.B25, PCI1.B31, PCI1.B36, PCI1.B41, PCI1.B43, PCI1.B54, PCI1.B59, PCI3.A10, PCI3.A14, PCI3.A16, PCI3.A21, PCI3.A27, PCI3.A33, PCI3.A39, PCI3.A45, PCI3.A53, PCI3.A59, PCI3.B19, PCI3.B25, PCI3.B31, PCI3.B36, PCI3.B41, PCI3.B43, PCI3.B54, PCI3.B59; also elsewhere on the board
P5V_PCI_A: C36.1, C44.1, C71.1, C73.1, PCI0.A5, PCI0.A8, PCI0.A61, PCI0.A62, PCI0.B5, PCI0.B6, PCI0.B61, PCI0.B62, PCI2.A5, PCI2.A8, PCI2.A61, PCI2.A62, PCI2.B5, PCI2.B6, PCI2.B61, PCI2.B62; also elsewhere on the board
P5V_PCI_B: C40.1, C48.1, C72.1, C74.1, PCI1.A5, PCI1.A8, PCI1.A61, PCI1.A62, PCI1.B5, PCI1.B6, PCI1.B61, PCI1.B62, PCI3.A5, PCI3.A8, PCI3.A61, PCI3.A62, PCI3.B5, PCI3.B6, PCI3.B61, PCI3.B62; also elsewhere on the board
P12V_PCI: C35.1, C39.1, C43.1, C47.1, PCI0.A2, PCI1.A2, PCI2.A2, PCI3.A2; also elsewhere on the board

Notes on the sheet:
Placement: Lo-Z: These capacitors provide AC return path for adjacent signals.
